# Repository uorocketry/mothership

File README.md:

# mothership
## Avionics Hardware IREC 2019

# Design blocks
 - Design blocks go in the `design blocks` directory
 - to use them with eagle add them from the `Control Panel` screen
  - From `Control Panel` click on `options > directories`
  - in the `directories` menu select the `design blocks` field, then click `browse` and find `mothership/design_blocks`
  - add the directory and click `ok`
  - now you should see the design blocks like this:

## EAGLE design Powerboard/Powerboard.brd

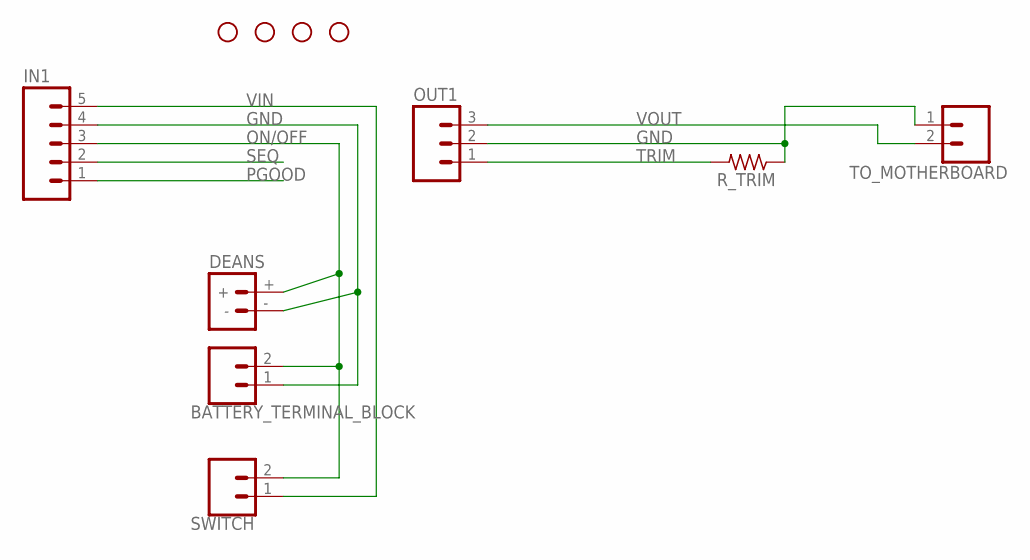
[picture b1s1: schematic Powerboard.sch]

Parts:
BATTERY_TERMINAL_BLOCK: CONN_023.5MM; SCREWTERMINAL-3.5MM-2
DEANS: BATTERY_CONN_DEANS; DEANS
IN1: M05PTH; 1X05
OUT1: M03PTH; 1X03
R_TRIM: R-US_R0603; R0603
SWITCH: CONN_023.5MM; SCREWTERMINAL-3.5MM-2
TO_MOTHERBOARD: CONN_023.5MM; SCREWTERMINAL-3.5MM-2
U$2, U$6, U$7, U$8: STAND-OFF

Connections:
GND: BATTERY_TERMINAL_BLOCK.1, DEANS.-, IN1.4, OUT1.2, R_TRIM.1, TO_MOTHERBOARD.1
ON/OFF: BATTERY_TERMINAL_BLOCK.2, DEANS.+, IN1.3, SWITCH.2
PGOOD: IN1.1
SEQ: IN1.2
TRIM: OUT1.1, R_TRIM.2
VIN: IN1.5, SWITCH.1
VOUT: OUT1.3, TO_MOTHERBOARD.2

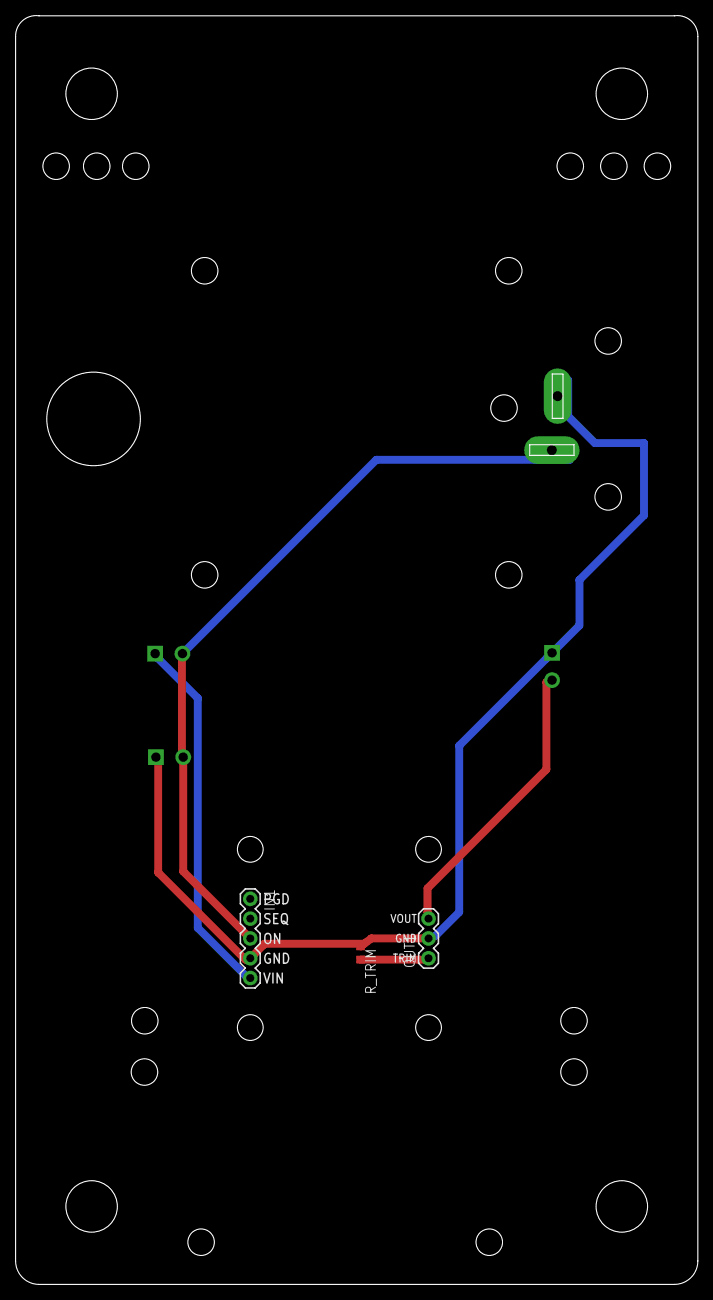
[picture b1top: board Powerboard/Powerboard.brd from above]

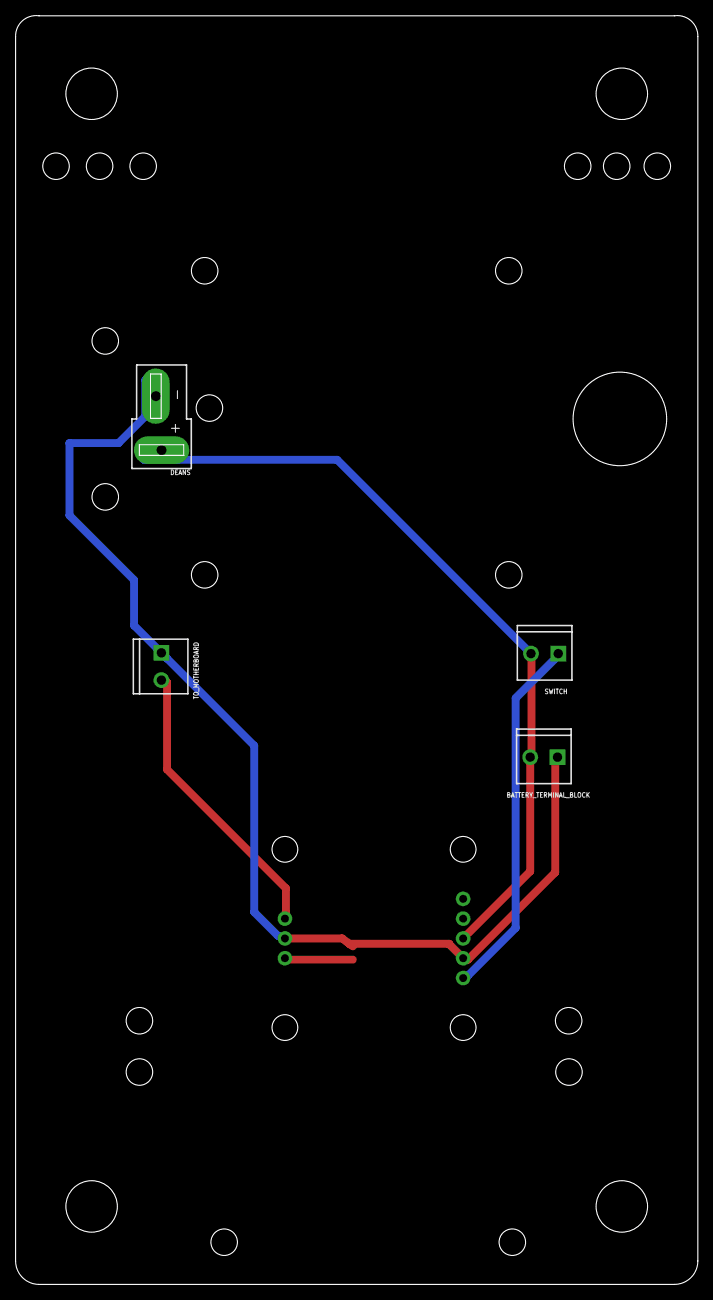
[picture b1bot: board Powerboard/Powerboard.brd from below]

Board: 2 copper layers, 87.5 x 162.7 mm, 11 parts (4 on the bottom side), 5 nets.

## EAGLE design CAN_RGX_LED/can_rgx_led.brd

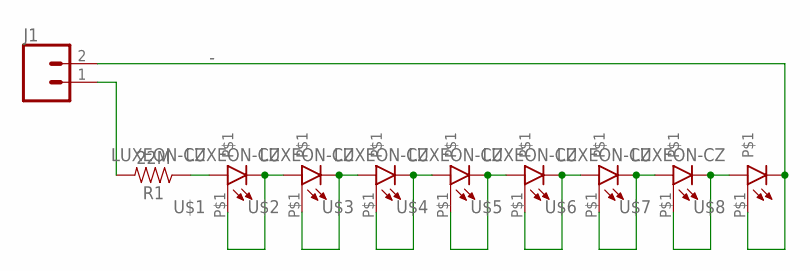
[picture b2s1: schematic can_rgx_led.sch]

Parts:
J1: CONN_02; 1X02
R1: 22M; 0603
U$1, U$2, U$3, U$4, U$5, U$6, U$7, U$8: LUXEON-CZ

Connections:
+: J1.1, R1.2
-: J1.2, U$8.P$1, U$8.P$3 (C)
unnamed: U$3.P$1, U$3.P$3 (C), U$4.P$2 (A)
unnamed: R1.1, U$1.P$2 (A)
unnamed: U$1.P$1, U$1.P$3 (C), U$2.P$2 (A)
unnamed: U$2.P$1, U$2.P$3 (C), U$3.P$2 (A)
unnamed: U$4.P$1, U$4.P$3 (C), U$5.P$2 (A)
unnamed: U$5.P$1, U$5.P$3 (C), U$6.P$2 (A)
unnamed: U$6.P$1, U$6.P$3 (C), U$7.P$2 (A)
unnamed: U$7.P$1, U$7.P$3 (C), U$8.P$2 (A)

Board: 2 copper layers, 10 parts (0 on the bottom side), 10 nets, no tracks yet.

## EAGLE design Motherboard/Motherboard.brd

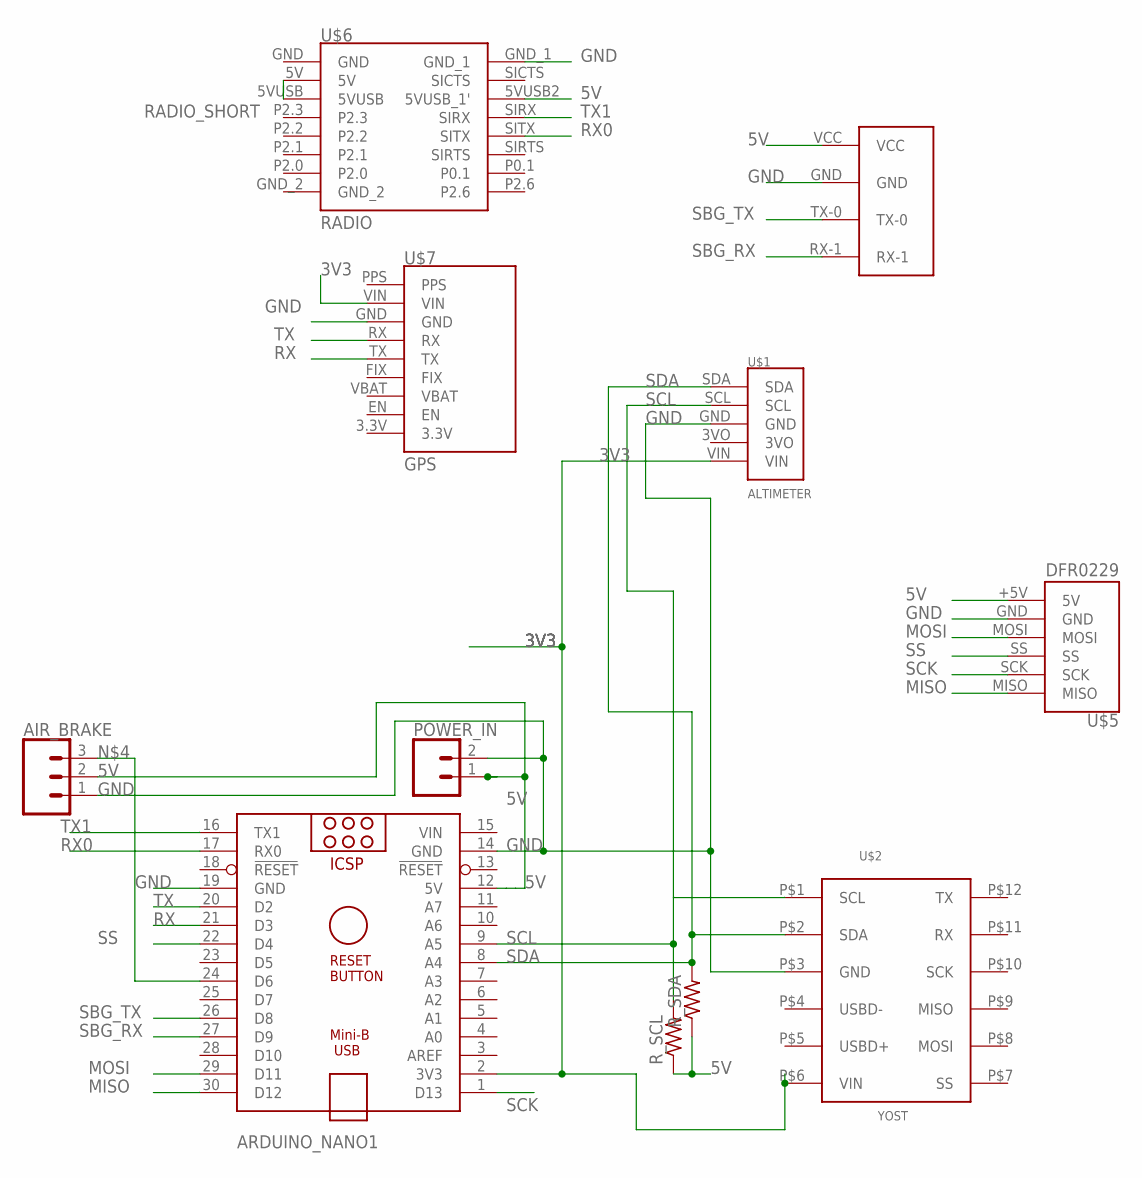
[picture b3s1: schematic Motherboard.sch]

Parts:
AIR_BRAKE: CONN_03; 1X03
ARDUINO_NANO1: ARDUINO_NANO
POWER_IN: CONN_023.5MM; SCREWTERMINAL-3.5MM-2
R_SCL: R-US_R0603; R0603
R_SDA: R-US_R0603; R0603
U$1: ALTIMETER
U$2: YOST
U$3: RS232
U$5: DFR0229
U$6: RADIO
U$7: GPS

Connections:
3V3: ARDUINO_NANO1.2 (3V3), U$1.VIN, U$2.P$6 (VIN), U$7.VIN
5V: AIR_BRAKE.2, ARDUINO_NANO1.12 (5V), POWER_IN.1, R_SCL.1, R_SDA.1, U$3.VCC, U$5.+5V (5V), U$6.5VUSB2 (5VUSB_1')
GND: AIR_BRAKE.1, ARDUINO_NANO1.14 (GND), ARDUINO_NANO1.19 (GND), POWER_IN.2, U$1.GND, U$2.P$3 (GND), U$3.GND, U$5.GND, U$6.GND_1, U$7.GND
MISO: ARDUINO_NANO1.30 (D12), U$5.MISO
MOSI: ARDUINO_NANO1.29 (D11), U$5.MOSI
unnamed: AIR_BRAKE.3, ARDUINO_NANO1.24 (D6)
RADIO_SHORT: U$6.5V, U$6.5VUSB
RX: ARDUINO_NANO1.21 (D3), U$7.TX
RX0: ARDUINO_NANO1.17 (RX0), U$6.SITX
SBG_RX: ARDUINO_NANO1.27 (D9), U$3.RX-1
SBG_TX: ARDUINO_NANO1.26 (D8), U$3.TX-0
SCK: ARDUINO_NANO1.1 (D13), U$5.SCK
SCL: ARDUINO_NANO1.9 (A5), R_SCL.2, U$1.SCL, U$2.P$1 (SCL)
SDA: ARDUINO_NANO1.8 (A4), R_SDA.2, U$1.SDA, U$2.P$2 (SDA)
SS: ARDUINO_NANO1.22 (D4), U$5.SS
TX: ARDUINO_NANO1.20 (D2), U$7.RX
TX1: ARDUINO_NANO1.16 (TX1), U$6.SIRX
VIN: ARDUINO_NANO1.15 (VIN)

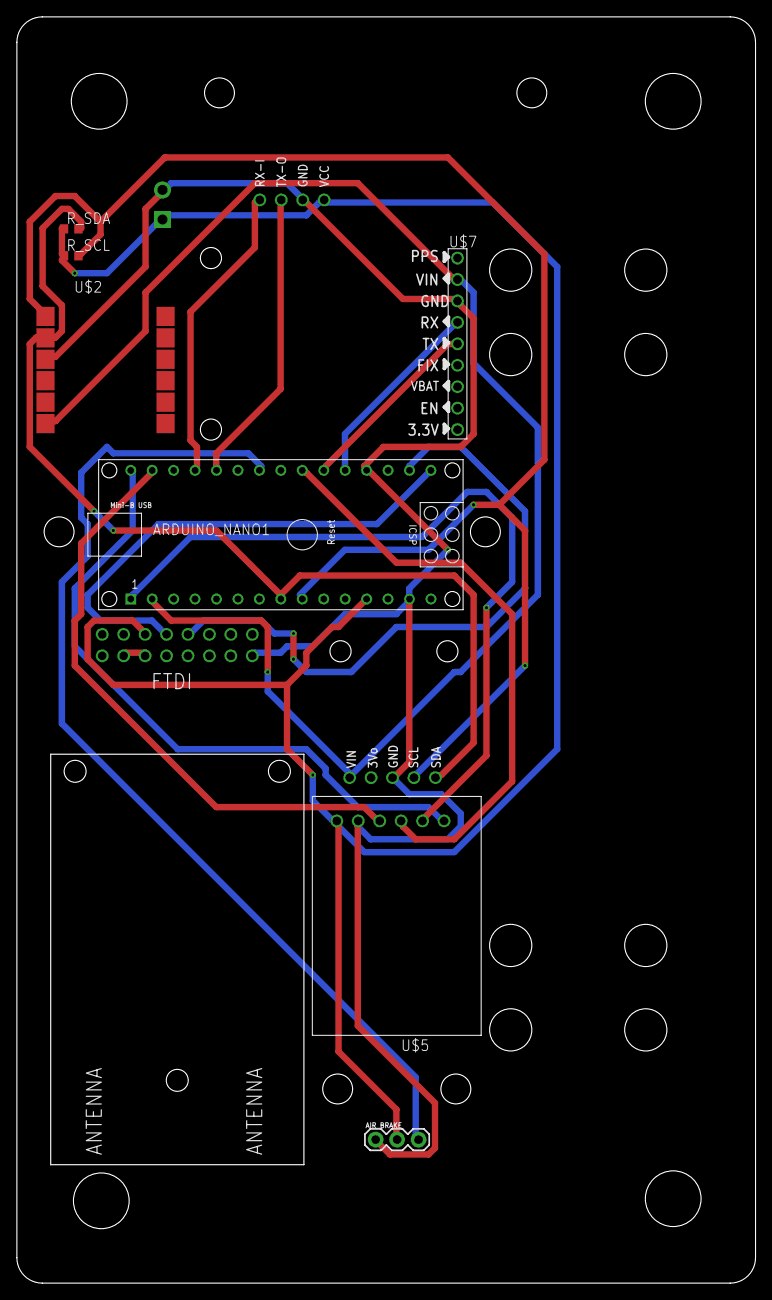
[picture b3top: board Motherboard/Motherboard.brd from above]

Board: 2 copper layers, 87.5 x 150.0 mm, 11 parts (1 on the bottom side), 17 nets.

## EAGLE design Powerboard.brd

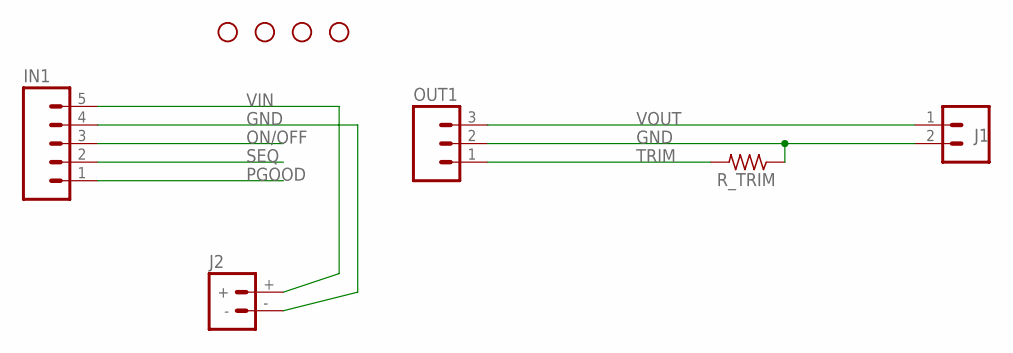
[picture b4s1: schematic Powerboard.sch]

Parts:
IN1: M05PTH; 1X05
J1: CONN_023.5MM; SCREWTERMINAL-3.5MM-2
J2: BATTERY_CONN_DEANS; DEANS
OUT1: M03PTH; 1X03
R_TRIM: R-US_R0603; R0603
U$2, U$6, U$7, U$8: STAND-OFF

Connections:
GND: IN1.4, J1.2, J2.-, OUT1.2, R_TRIM.1
ON/OFF: IN1.3
PGOOD: IN1.1
SEQ: IN1.2
TRIM: OUT1.1, R_TRIM.2
VIN: IN1.5, J2.+
VOUT: J1.1, OUT1.3

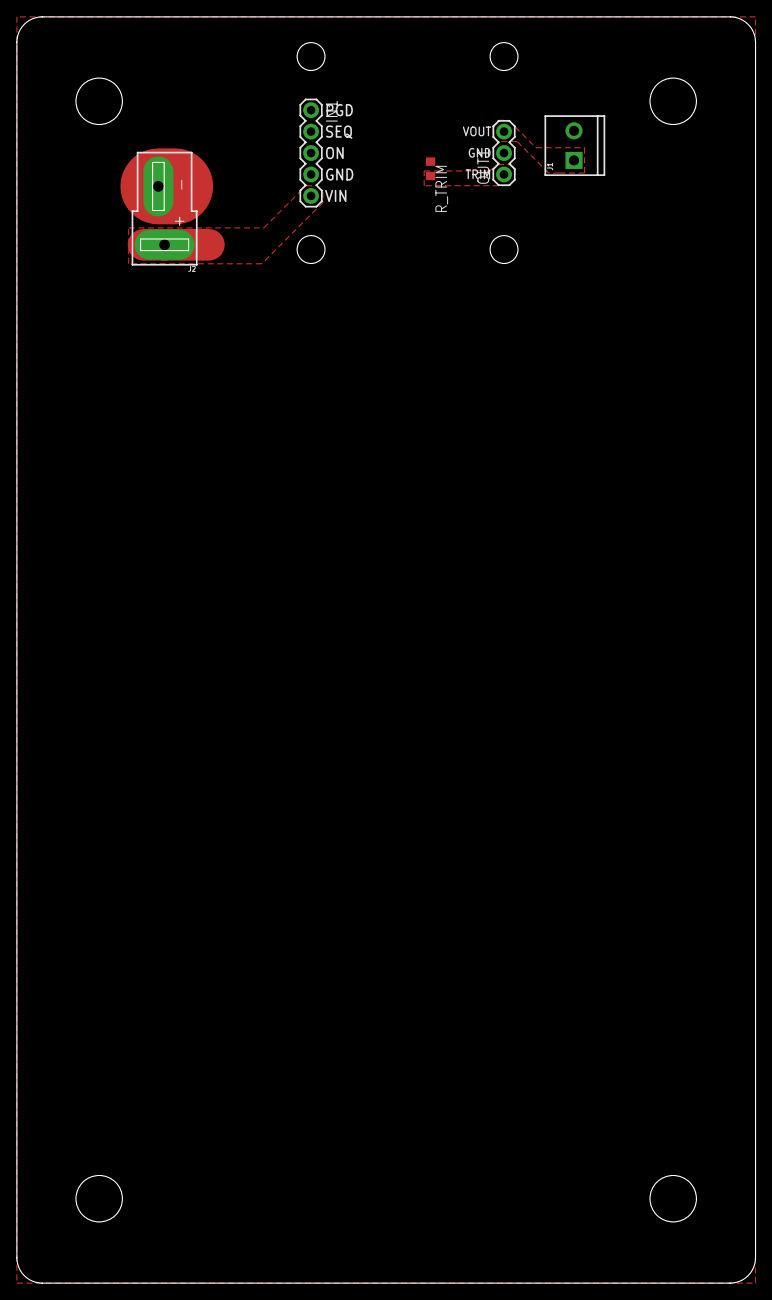
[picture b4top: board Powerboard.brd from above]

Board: 2 copper layers, 87.5 x 150.0 mm, 9 parts (0 on the bottom side), 4 nets.

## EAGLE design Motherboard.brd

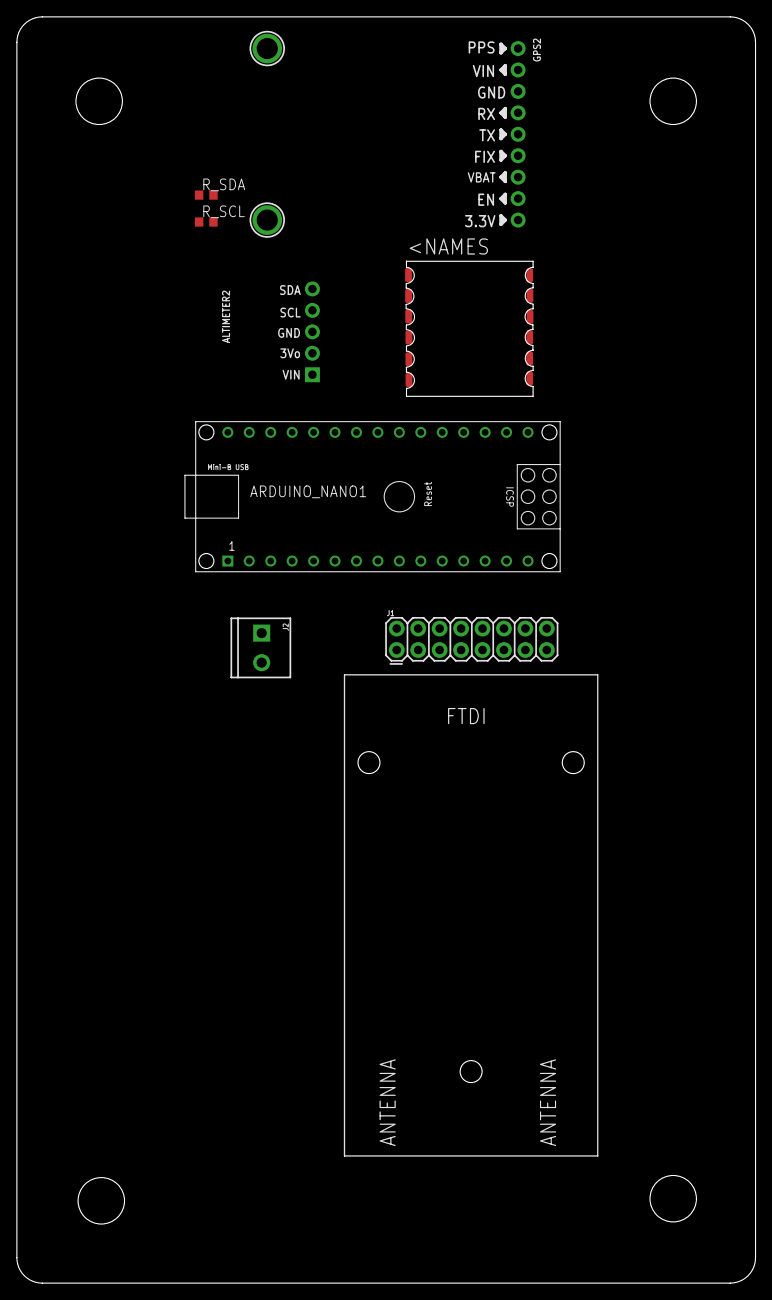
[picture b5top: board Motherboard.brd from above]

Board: 2 copper layers, 87.5 x 150.0 mm, 11 parts (0 on the bottom side), 6 nets, no tracks yet.

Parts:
ALTIMETER2: 1X05_ROUND_70
ARDUINO_NANO1: ARDUINO_NANO
GPS2: 1X09_ROUND_70
IMU: YOSTLABSIMU
J1: 2X8
J2: SCREWTERMINAL-3.5MM-2
R_SCL: R0603
R_SDA: R0603
U$1: RADIO
U$3, U$4: MOUNTINGHOLE2.5; MOUNTINGHOLE_2.5_PLATED

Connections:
3V3: ALTIMETER2.1, ARDUINO_NANO1.2, GPS2.1, IMU.VIN, R_SCL.1, R_SDA.1
GND: ALTIMETER2.3, ARDUINO_NANO1.14, ARDUINO_NANO1.19, GPS2.7, IMU.GND
RX: ARDUINO_NANO1.21, GPS2.5
SCL: ALTIMETER2.4, ARDUINO_NANO1.9, IMU.SCL, R_SCL.2
SDA: ALTIMETER2.5, ARDUINO_NANO1.8, IMU.SDA, R_SDA.2
TX: ARDUINO_NANO1.20, GPS2.6

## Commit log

2018-10-04 add design blocks
2018-10-10 add gps block
2018-10-10 gitignore
2018-10-10 add altimeter block
2018-10-11 test
2018-10-11 Add Arduino Library
2018-10-16 Cleaned up the three dbl files
2018-11-01 Add files via upload
    Created custom block diagram of YOST Labs IMU.
2018-11-10 Connected pins in schematic file
2018-11-15 add buck converter
2018-11-15 cleanup
2018-11-19 more circuit
2019-01-29 more
2019-01-31 add-filets
2019-01-31 routing powerboard
2019-01-31 keepout
2019-01-31 powerboard
2019-02-01 Rewire Powerboard
2019-03-05 refactor
2019-03-16 add SD card, wire radio
2019-03-18 library updates
2019-03-18 add components to boards
2019-03-19 more layout
2019-03-19 powerboard layout
2019-03-19 routing
2019-03-19 more routing
2019-03-20 review1
2019-03-27 layout r2
2019-03-27 route powerboard r2
2019-03-27 routed motherboard r2
2019-04-28 final revisions
2019-11-17 Pi 4 device
2019-11-18 added rpi4 design
2020-01-07 Fix rpi library footprint
2020-01-28 add LED footprint and LED board
2020-01-29 board 1_0
2020-01-30 switch LED package
2020-02-02 extended powerboard
2020-02-02 connect middle to anodes as suggested by ayman
2020-02-23 added holes, needs review

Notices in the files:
parts and their libraries:
SparkFun-Connectors: Licensing: Creative Commons ShareAlike 4.0 International - https://creativecommons.org/licenses/by-sa/4.0
